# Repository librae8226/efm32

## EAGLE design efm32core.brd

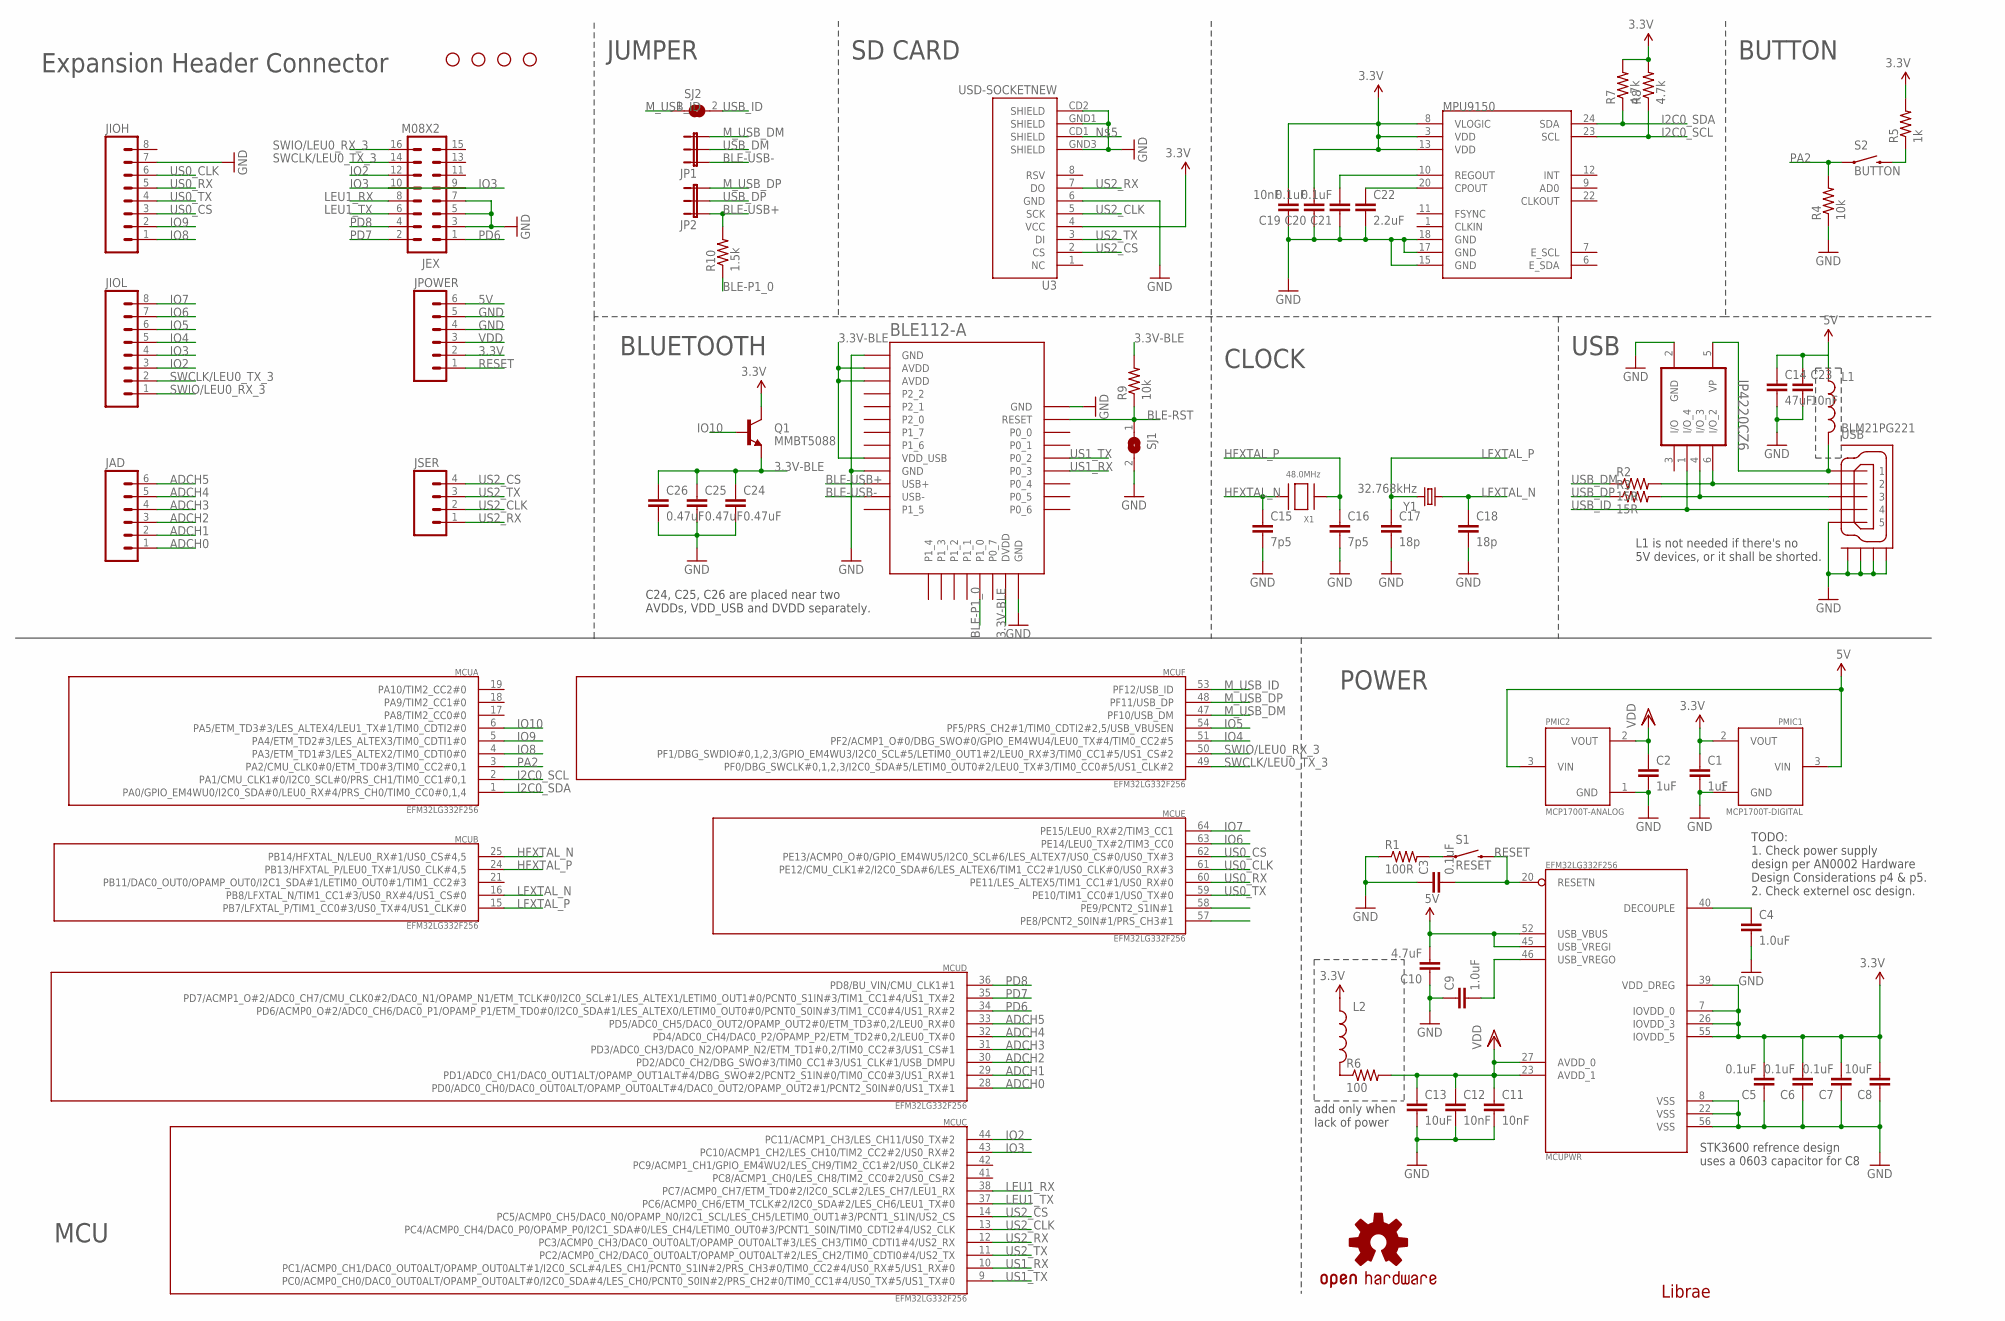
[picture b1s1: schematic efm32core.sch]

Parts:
BLE112-A: SF-BLUEGIGA_BLE112-A-VISUAL; SF-BLUEGIGA_BLE112-A
C1, C2: 1uF; 1206
C3, C5, C6, C7, C20, C21: 0.1uF; 0603-CAP
C4, C9: 1.0uF; 0603-CAP
C8, C13: 10uF; 1206
C10: 4.7uF; 0603-CAP
C11, C12, C19, C23: 10nF; 0603-CAP
C14: 47uF; 1206
C15, C16: 7p5; 0603-CAP
C17, C18: 18p; 0603-CAP
C22: 2.2uF; 0603-CAP
C24, C25, C26: 0.47uF; 0603-CAP
IP4220CZ6: IP4220CZ6SSOT-6; SOT95P275X110-6N
JAD: M06SIP; 1X06
JEX: M08X2; 2X8
JIOH: M081X08; 1X08
JIOL: M081X08; 1X08
JP1, JP2: JUMPER-3SMD; SJ_3
JPOWER: M06SIP; 1X06
JSER: M041.27MM; 1X04-1.27MM
L1: BLM21PG221; 0805
L2: INDUCTOR0603; 0603
LOGO1: OSHW-LOGOL; OSHW-LOGO-L
MCU: EFM32LG332F256; QFP64
MPU9150: MPU-9150QFN-24-NP; QFN-24-NP
PMIC1: MCP1700T-DIGITAL; SOT23
PMIC2: MCP1700T-ANALOG; SOT23
Q1: MMBT5088; SOT23
R1: 100R; 0603-RES
R2, R3: 15R; 0603-RES
R4, R9: 10k; 0603-RES
R5: 1k; 0603-RES
R6: 100; 0603-RES
R7, R8: 4.7k; 0603-RES
R10: 1.5k; 0603-RES
S1: RESET; PIXHAWK2_EVQP7J01K
S2: BUTTON; PIXHAWK2_EVQP7J01K
SJ1, SJ2: JUMPER_SJ
STANDOFF1, STANDOFF2, STANDOFF3, STANDOFF4: STAND-OFF
U3: USD-SOCKETNEW; MICRO-SD-SOCKET-PP
USB: PIXHAWK2_MOLEX-47346-0001
X1: 48.0MHz; NX5032
Y1: 32.768kHz; CRYSTAL-32KHZ-SMD-MS3V-T1R

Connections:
1: IP4220CZ6.5 (VP), L1.2, USB.VBUS (1)
3.3V: C1.1, C5.2, C6.2, C7.2, C8.2, C19.2, C20.2, JPOWER.2, L2.1, MCU.7 (IOVDD_0), MCU.26 (IOVDD_3), MCU.39 (VDD_DREG), MCU.55 (IOVDD_5), MPU9150.3 (VDD), MPU9150.8 (VLOGIC), MPU9150.13 (VDD), PMIC1.2 (VOUT), Q1.3 (C), R5.2, R7.2, R8.2, U3.4 (VCC)
3.3V-BLE: BLE112-A.AVDD1 (AVDD), BLE112-A.AVDD2 (AVDD), BLE112-A.DVDD, BLE112-A.VDD_USB, C24.1, C25.1, C26.1, Q1.2 (E), R9.2
5V: C10.2, C14.1, C23.1, JPOWER.6, L1.1, MCU.45 (USB_VREGI), MCU.52 (USB_VBUS), PMIC1.3 (VIN), PMIC2.3 (VIN)
ADCH0: JAD.1, MCU.28 (PD0/ADC0_CH0/DAC0_OUT0ALT/OPAMP_OUT0ALT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)
ADCH1: JAD.2, MCU.29 (PD1/ADC0_CH1/DAC0_OUT1ALT/OPAMP_OUT1ALT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)
ADCH2: JAD.3, MCU.30 (PD2/ADC0_CH2/DBG_SWO#3/TIM0_CC1#3/US1_C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)
ADCH3: JAD.4, MCU.31 (PD3/ADC0_CH3/DAC0_N2/OPAMP_N2/ETM_TD1#0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)
ADCH4: JAD.5, MCU.32 (PD4/ADC0_CH4/DAC0_P2/OPAMP_P2/ETM_TD2#0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)
ADCH5: JAD.6, MCU.33 (PD5/ADC0_CH5/DAC0_OUT2/OPAMP_OUT2#0/ETM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)
BLE-P1_0: BLE112-A.P1_0, R10.1
BLE-RST: BLE112-A.RESET, R9.1, SJ1.1
BLE-USB+: BLE112-A.USB+, JP2.1, R10.2
BLE-USB-: BLE112-A.USB-, JP1.1
GND: BLE112-A.GND1 (GND), BLE112-A.GND2 (GND), BLE112-A.GND3 (GND), BLE112-A.GND4 (GND), C1.2, C2.2, C3.1, C4.2, C5.1, C6.1, C7.1, C8.1, C9.1, C10.1, C11.2, C12.2, C13.2, C14.2, C15.2, C16.2, C17.2, C18.2, C19.1, C20.1, C21.1, C22.2, C23.2, C24.2, C25.2, C26.2, IP4220CZ6.2 (GND), JEX.3, JEX.5, JEX.7, JIOH.7, JPOWER.4, JPOWER.5, MCU.8 (VSS), MCU.22 (VSS), MCU.56 (VSS), MPU9150.15 (GND), MPU9150.17 (GND), MPU9150.18 (GND), PMIC1.1 (GND), PMIC2.1 (GND), R1.1, R4.1, SJ1.2, U3.6 (GND), U3.CD2 (SHIELD), U3.GND1 (SHIELD), U3.GND3 (SHIELD), USB.GND (5), USB.GND1, USB.GND2, USB.GND3, USB.GND4
HFXTAL_N: C15.1, MCU.25 (PB14/HFXTAL_N/LEU0_RX#1/US0_CS#4,5), X1.P$2
HFXTAL_P: C16.1, MCU.24 (PB13/HFXTAL_P/LEU0_TX#1/US0_CLK#4,5), X1.P$1
I2C0_SCL: MCU.2 (PA1/CMU_CLK1#0/I2C0_SCL#0/PRS_CH1/TIM0_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), MPU9150.23 (SCL), R8.1
I2C0_SDA: MCU.1 (PA0/GPIO_EM4WU0/I2C0_SDA#0/LEU0_RX#4/PR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), MPU9150.24 (SDA), R7.1
IO2: JEX.12, JIOL.3, MCU.44 (PC11/ACMP1_CH3/LES_CH11/US0_TX#2)
IO3: JEX.9, JEX.10, JIOL.4, MCU.43 (PC10/ACMP1_CH2/LES_CH10/TIM2_CC2#2/US0_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)
IO4: JIOL.5, MCU.51 (PF2/ACMP1_O#0/DBG_SWO#0/GPIO_EM4WU4/LEU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)
IO5: JIOL.6, MCU.54 (PF5/PRS_CH2#1/TIM0_CDTI2#2,5/USB_VBUSEN)
IO6: JIOL.7, MCU.63 (PE14/LEU0_TX#2/TIM3_CC0)
IO7: JIOL.8, MCU.64 (PE15/LEU0_RX#2/TIM3_CC1)
IO8: JIOH.1, MCU.4 (PA3/ETM_TD1#3/LES_ALTEX2/TIM0_CDTI0#0)
IO9: JIOH.2, MCU.5 (PA4/ETM_TD2#3/LES_ALTEX3/TIM0_CDTI1#0)
IO10: MCU.6 (PA5/ETM_TD3#3/LES_ALTEX4/LEU1_TX#1/TIM0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), Q1.1 (B)
LEU1_RX: JEX.8, MCU.38 (PC7/ACMP0_CH7/ETM_TD0#2/I2C0_SCL#2/LES_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)
LEU1_TX: JEX.6, MCU.37 (PC6/ACMP0_CH6/ETM_TCLK#2/I2C0_SDA#2/LES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)
LFXTAL_N: C18.1, MCU.16 (PB8/LFXTAL_N/TIM1_CC1#3/US0_RX#4/US1_CS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), Y1.X1 (1)
LFXTAL_P: C17.1, MCU.15 (PB7/LFXTAL_P/TIM1_CC0#3/US0_TX#4/US1_CL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), Y1.X2 (2)
M_USB_DM: JP1.3, MCU.47 (PF10/USB_DM)
M_USB_DP: JP2.3, MCU.48 (PF11/USB_DP)
M_USB_ID: MCU.53 (PF12/USB_ID), SJ2.1
unnamed: L2.2, R6.1
unnamed: R1.2, S1.A1 (1)
unnamed: C4.1, MCU.40 (DECOUPLE)
unnamed: C9.2, MCU.46 (USB_VREGO)
unnamed: R5.1, S2.B3 (2)
unnamed: C21.2, MPU9150.10 (REGOUT)
unnamed: IP4220CZ6.4 (I/O_3), R3.2, USB.D+ (3)
unnamed: IP4220CZ6.6 (I/O_2), R2.2, USB.D- (2)
unnamed: C22.1, MPU9150.20 (CPOUT)
PA2: MCU.3 (PA2/CMU_CLK0#0/ETM_TD0#3/TIM0_CC2#0,1), R4.2, S2.A1 (1)
PD6: JEX.1, MCU.34 (PD6/ACMP0_O#2/ADC0_CH6/DAC0_P1/OPAMP_P1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)
PD7: JEX.2, MCU.35 (PD7/ACMP1_O#2/ADC0_CH7/CMU_CLK0#2/DAC0_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)
PD8: JEX.4, MCU.36 (PD8/BU_VIN/CMU_CLK1#1)
RESET: C3.2, JPOWER.1, MCU.20 (RESETN), S1.B3 (2)
SWCLK/LEU0_TX_3: JEX.14, JIOL.2, MCU.49 (PF0/DBG_SWCLK#0,1,2,3/I2C0_SDA#5/LETIM0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)
SWIO/LEU0_RX_3: JEX.16, JIOL.1, MCU.50 (PF1/DBG_SWDIO#0,1,2,3/GPIO_EM4WU3/I2C0_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)
US0_CLK: JIOH.6, MCU.61 (PE12/CMU_CLK1#2/I2C0_SDA#6/LES_ALTEX6/T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)
US0_CS: JIOH.3, MCU.62 (PE13/ACMP0_O#0/GPIO_EM4WU5/I2C0_SCL#6/L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)
US0_RX: JIOH.5, MCU.60 (PE11/LES_ALTEX5/TIM1_CC1#1/US0_RX#0)
US0_TX: JIOH.4, MCU.59 (PE10/TIM1_CC0#1/US0_TX#0)
US1_RX: BLE112-A.P0_3, MCU.10 (PC1/ACMP0_CH1/DAC0_OUT0ALT/OPAMP_OUT0AL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)
US1_TX: BLE112-A.P0_2, MCU.9 (PC0/ACMP0_CH0/DAC0_OUT0ALT/OPAMP_OUT0AL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)
US2_CLK: JSER.2, MCU.13 (PC4/ACMP0_CH4/DAC0_P0/OPAMP_P0/I2C1_SDA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), U3.5 (SCK)
US2_CS: JSER.4, MCU.14 (PC5/ACMP0_CH5/DAC0_N0/OPAMP_N0/I2C1_SCL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), U3.2 (CS)
US2_RX: JSER.1, MCU.12 (PC3/ACMP0_CH3/DAC0_OUT0ALT/OPAMP_OUT0AL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), U3.7 (DO)
US2_TX: JSER.3, MCU.11 (PC2/ACMP0_CH2/DAC0_OUT0ALT/OPAMP_OUT0AL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), U3.3 (DI)
USB_DM: JP1.2, R2.1
USB_DP: JP2.2, R3.1
USB_ID: IP4220CZ6.1 (I/O_4), SJ2.2, USB.ID (4)
VDD: C2.1, C11.1, C12.1, C13.1, JPOWER.3, MCU.23 (AVDD_1), MCU.27 (AVDD_0), PMIC2.2 (VOUT), R6.2

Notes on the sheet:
Expansion Header Connector
Librae
MCU
STK3600 refrence design uses a 0603 capacitor for C8
USB
POWER
add only when lack of power
CLOCK
TODO: 1. Check power supply design per AN0002 Hardware Design Considerations p4 & p5. 2. Check externel osc design.
BLUETOOTH
SD CARD
BUTTON
L1 is not needed if there's no 5V devices, or it shall be shorted.
C24, C25, C26 are placed near two AVDDs, VDD_USB and DVDD separately.
JUMPER

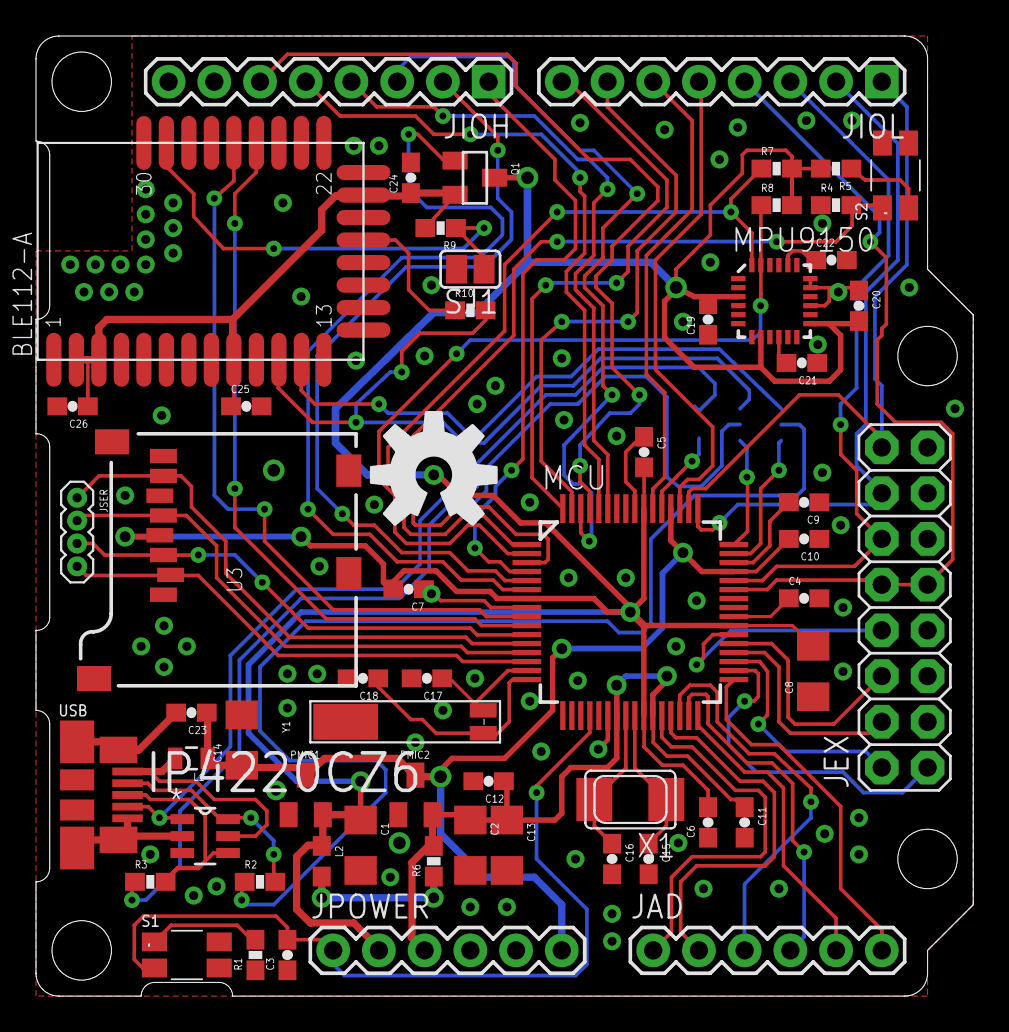
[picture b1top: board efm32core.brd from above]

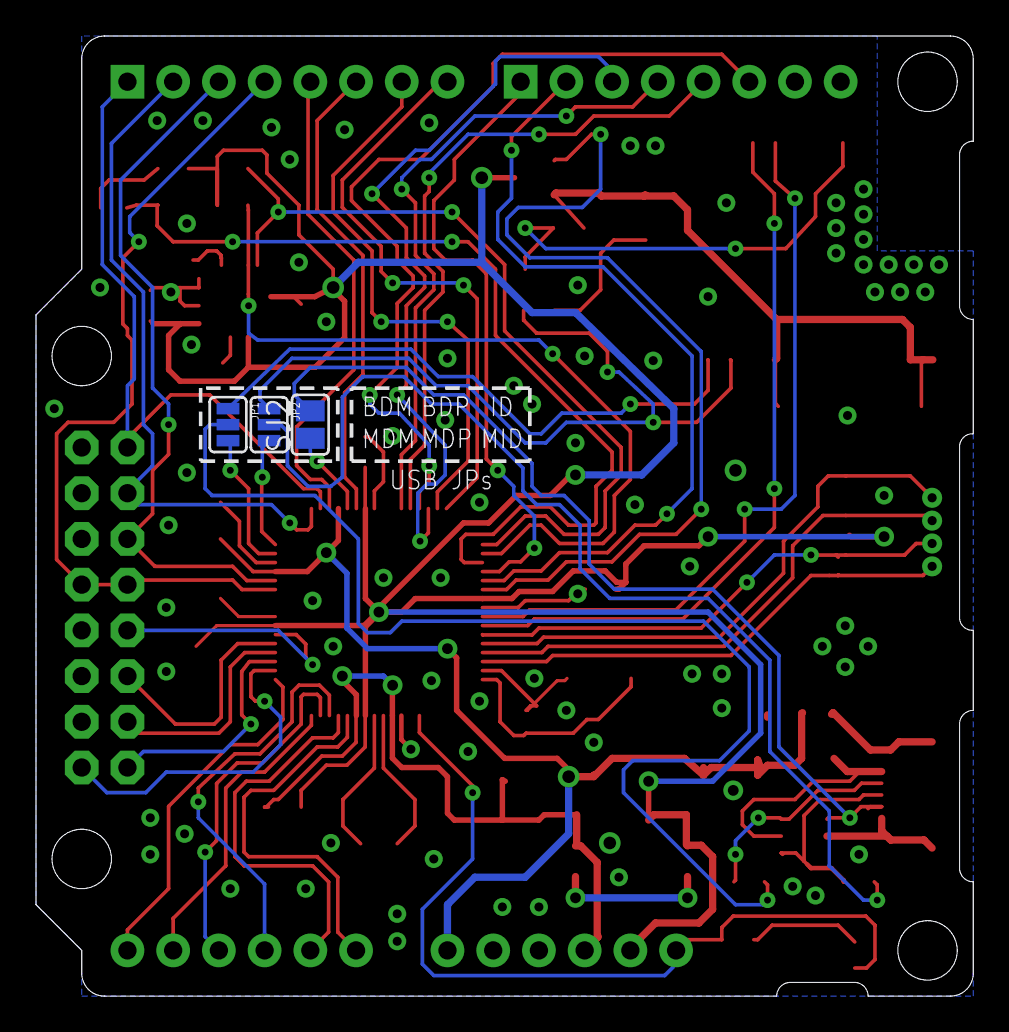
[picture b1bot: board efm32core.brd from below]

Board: 2 copper layers, 52.1 x 53.3 mm, 66 parts (3 on the bottom side), 65 nets.

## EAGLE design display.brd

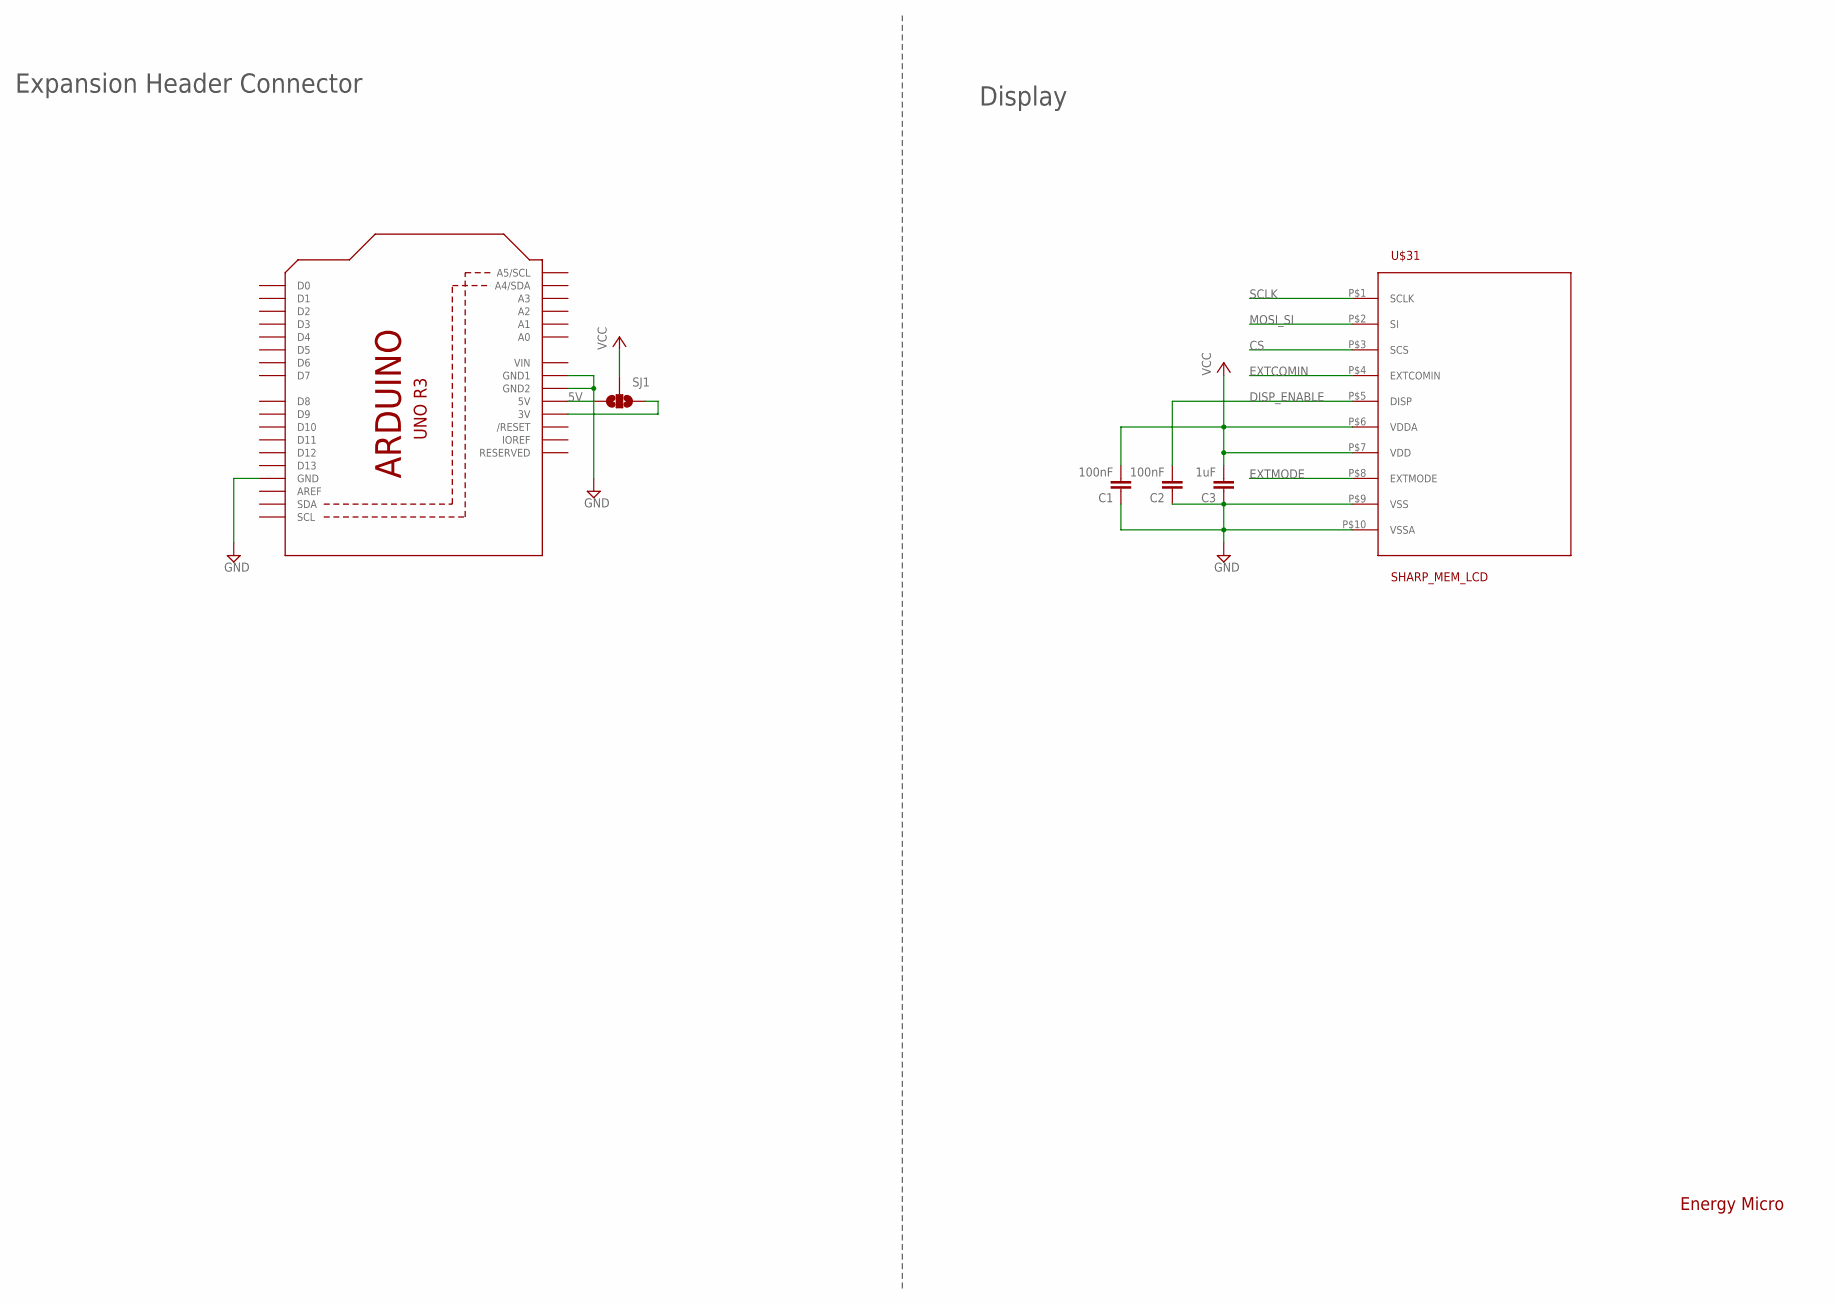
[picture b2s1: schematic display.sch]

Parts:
C1, C2: 100nF; C0402K
C3: 1uF; C0402K
SJ1: SOLDERJUMPER_2WAYT; SJ_2
U1: ARDUINOR3-MINI
U$31: SHARP_MEM_LCD

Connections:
5V: SJ1.3, U1.5V
CS: U$31.P$3 (SCS)
DISP_ENABLE: C2.2, U$31.P$5 (DISP)
EXTCOMIN: U$31.P$4 (EXTCOMIN)
EXTMODE: U$31.P$8 (EXTMODE)
GND: C1.1, C2.1, C3.1, U1.GND, U1.GND1, U1.GND2, U$31.P$9 (VSS), U$31.P$10 (VSSA)
MOSI_SI: U$31.P$2 (SI)
SCLK: U$31.P$1 (SCLK)
VCC: C1.2, C3.2, SJ1.2, U$31.P$6 (VDDA), U$31.P$7 (VDD)
VIN: U1.VIN
VMCU_3V3: SJ1.1, U1.3V

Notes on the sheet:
Expansion Header Connector
Display
Energy Micro

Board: 2 copper layers, 7 parts (1 on the bottom side), 5 nets, no tracks yet.

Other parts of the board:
U$6: GECKO_SOLDER_MASK_TOP

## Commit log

2013-10-31 first commit - forked from efm32 community:
    http://forum.energymicro.com/index.php?app=core&module=attach&section=attach&attach_id=227
2013-11-01 do cleanups
2013-11-02 update Docu color
2013-11-10 do cleanups, draw frame
2013-11-10 marching on
2013-11-10 optimize board shape
2013-11-11 modulize, update power and usb
2013-11-11 optimize a bit
2013-11-12 update a bit
2013-11-12 layout components
2013-11-12 add up bluetooth module and microsd socket
2013-11-14 update a bit of position
2013-11-16 complete connections
2013-11-16 update component name
2013-11-16 do some fixes and updates
    1. Fix L1 option.
    2. Add a cap for bluetooth module.
2013-11-17 add the display module daughter board
2013-11-25 update bluetooth and add co mcu
    1. use a smaller footprint ble module
    2. add a low power co cpu
2013-11-26 temporary update
2013-11-27 update bluetooth module, replace with BLE112
2013-11-27 update PCB layout (part off)
2013-11-28 do some line ups
2013-11-28 add polygon
2013-11-29 connect some routes
2013-11-29 route
2013-11-29 route accel
2013-12-02 optimize some routes
2013-12-02 optimize
2013-12-28 layout wires
2013-12-30 layout and refine wires
2013-12-31 some refines
2013-12-31 layout wires, needs refine
2013-12-31 update swd wires
2014-01-08 almost done
2014-01-11 refine

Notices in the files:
parts and their libraries:
EnergyMicro: CC0 License
SparkFun-Connectors: Licensing: CC v3.0 Share-Alike You are welcome to use this library for commercial purposes.
